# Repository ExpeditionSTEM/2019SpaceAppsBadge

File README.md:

# 2019SpaceAppsBadge
PLEASE STAY TUNED FOR UPDATES!  I WILL GET THIS REPO UPDATED BY 10/29.

A description of the 2019 Space Apps Trophy made for the Huntsville Main Stage

LIST OF COMPONENTS:

CUSTOM:

Custom Printed Circuit Board (PCB) - Designed by Andrew Denio. Produced by JLCPCB.com See "EAGLE" folder for files.

ATTINY 85-20PU Microcontroller 8 pin DIP: https://www.amazon.com/gp/product/B06W9JBJJ6

SSD1306 128x32 pixel i2c OLED Display https://www.amazon.com/gp/product/B07WHVYWXS/

3xAAA Enclosed Battery Case https://www.amazon.com/gp/product/B07M8RV9DC

MISC:

Photoresistor (Light Sensor) 5 mm GM5539 5539 https://www.amazon.com/dp/B01N7V536K

Slide Switch 3 Pin 2 Position SPDT with PCB Panel for Arduino 0.5 Amp, 50V DC, 2 mm https://www.amazon.com/gp/product/B079D58DB3/

FROM JLCPCB (mounted through SMT assembly):

WS2812B-V3 - 5050 LIGHT EMITTING DIODE (LED) RED/GREEN/BLUE SMD

8 pin Female Header to re-flash ATTINY chip

FOR 'THROUGH-HOLE' BOARD:

470 OHM 1/4 Watt resistor

10 KOHM 1/4 Watt resistor

6mm x 6mm Tactile Buttons

10uF 25V Capacitor

FOR 'SMD' BOARD:

TACTILE SWITCHES SPST 5.10MM X 5.10MM 0.40MM 50MA @ 12VDC SMD

Multilayer Ceramic Capacitor - SMD/SMT 10UF 25V 0805 ROHS

CHIP RESISTOR - SURFACE MOUNT 10KOHMS ±1% 1/8W 0805 ROHS

CHIP RESISTOR - SURFACE MOUNT 470OHMS ±1% 1/8W 0805 ROHS

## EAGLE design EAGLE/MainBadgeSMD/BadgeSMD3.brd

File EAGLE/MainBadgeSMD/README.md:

This is the badge that was 'fully' assembled.  Most of the badge was assembled by JLCPCB, but some components were hand soldered/mounted.

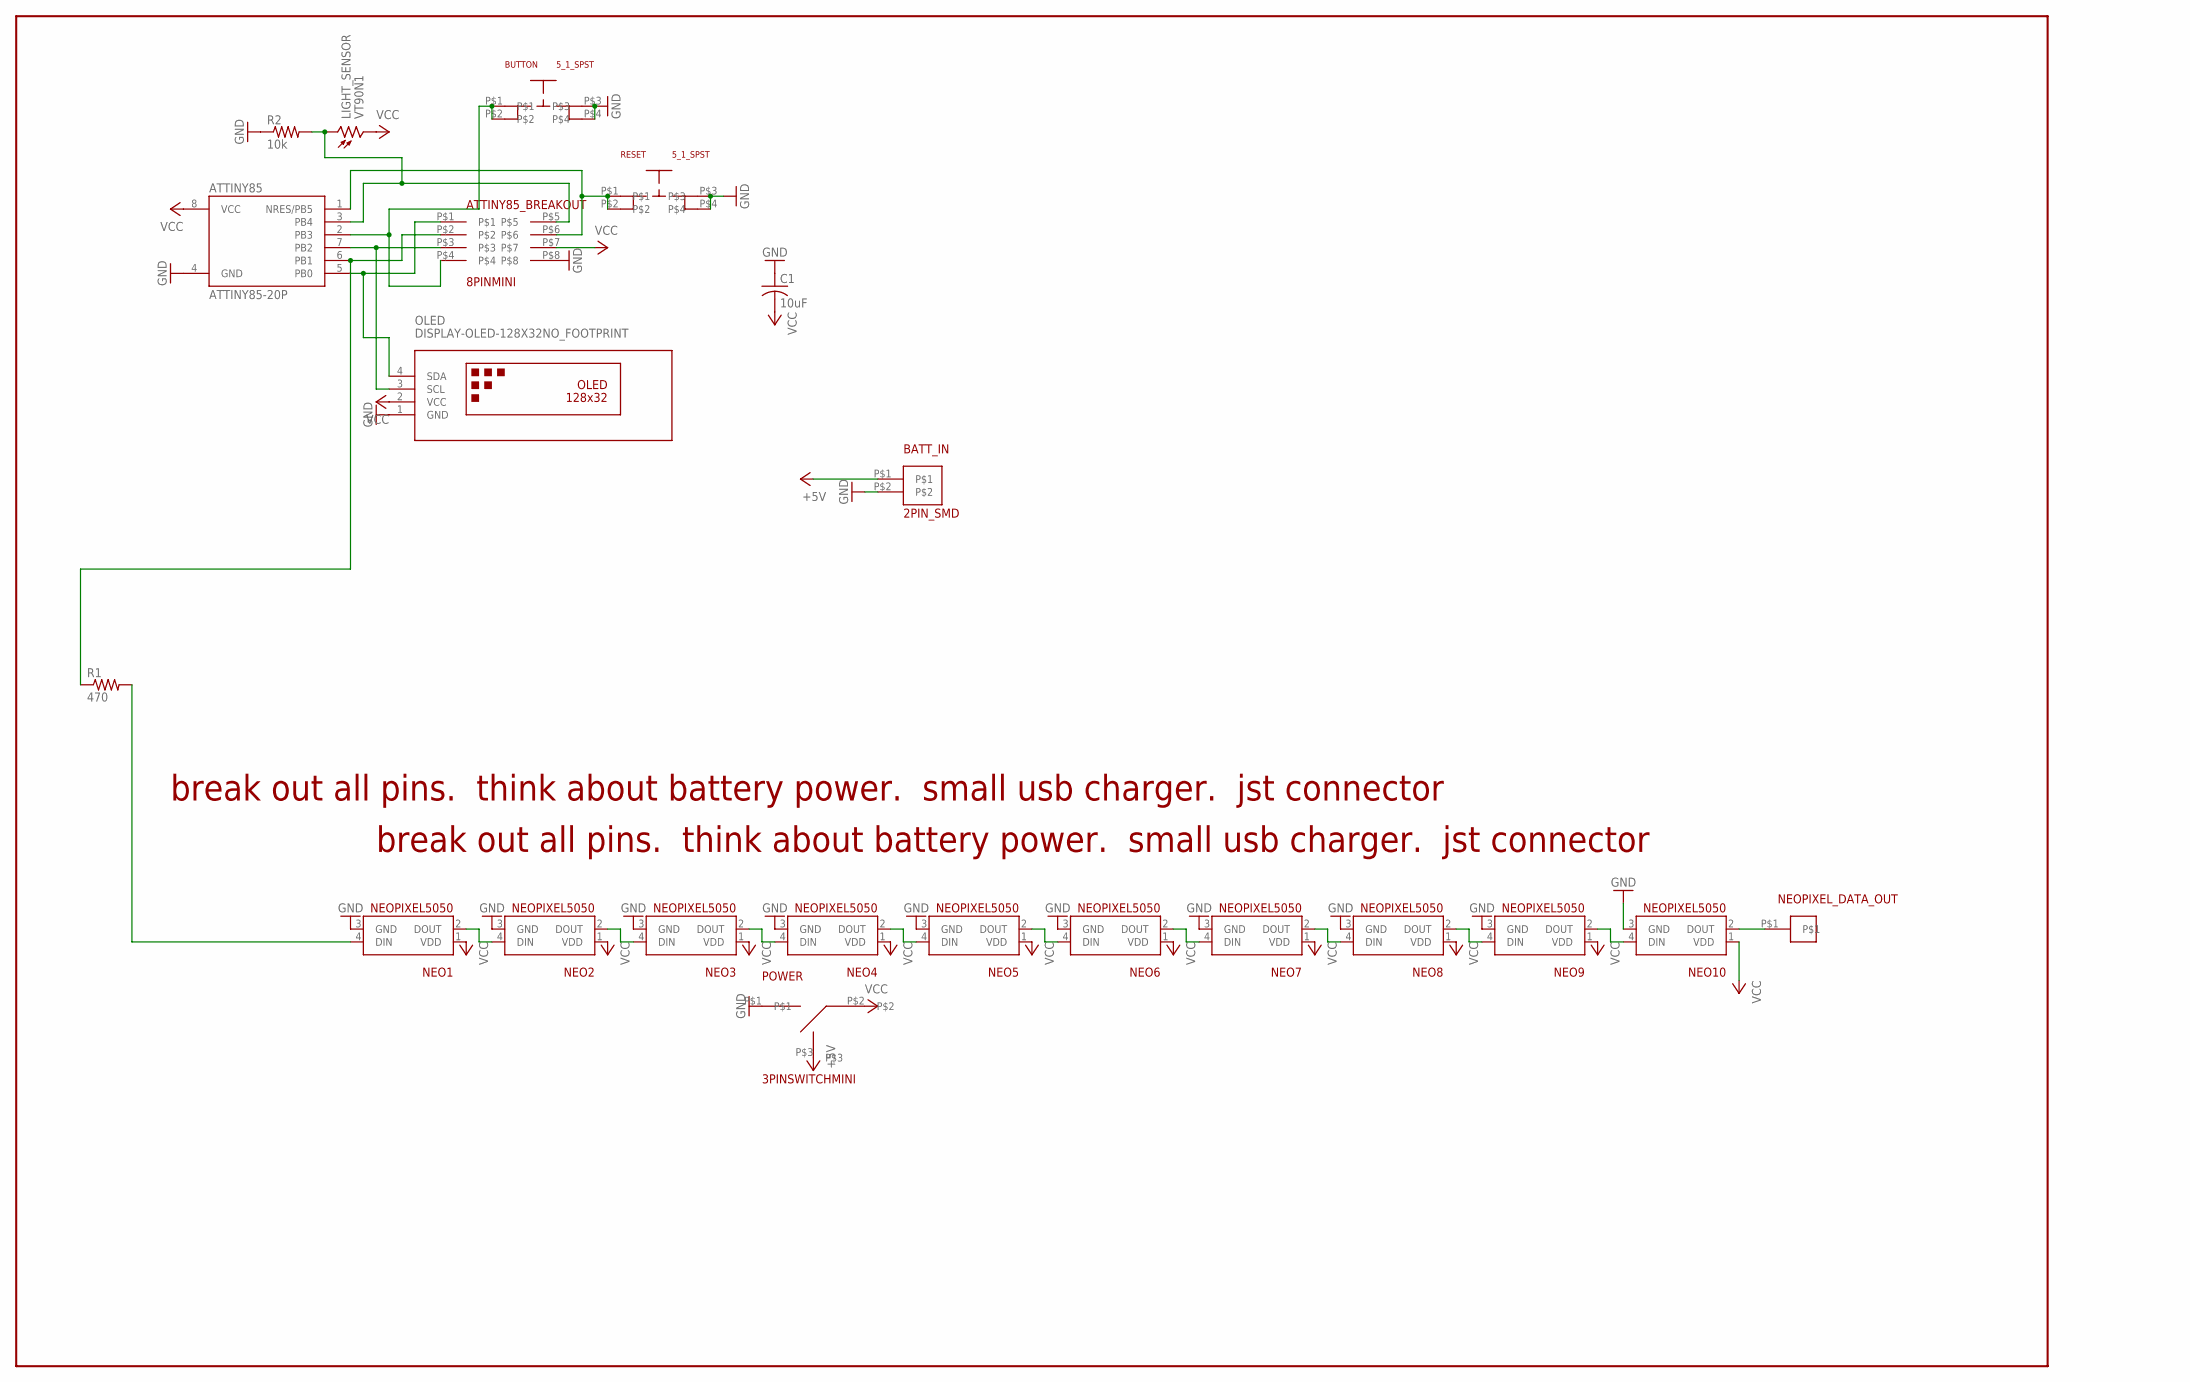
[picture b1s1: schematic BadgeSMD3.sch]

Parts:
ATTINY85: ATTINY85-20P; PDIP08_300MIL
ATTINY85_BREAKOUT: 8PINMINI
BATT_IN: 2PIN_SMD
BUTTON: 5_1_SPST
C1: 10uF; C0805
LIGHT_SENSOR: VT90N1; VT900
NEO1, NEO2, NEO3, NEO4, NEO5, NEO6, NEO7, NEO8, NEO9, NEO10: NEOPIXEL5050
NEOPIXEL_DATA_OUT: 1PINMINI
OLED: DISPLAY-OLED-128X32NO_FOOTPRINT; DISPLAY-OLED-128X32_NO_FOOTPRINT
POWER: 3PINSWITCHMINI; 3PINMINI
R1: 470; M0805
R2: 10k; M0805
RESET: 5_1_SPST

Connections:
+5V: BATT_IN.P$1, POWER.P$3
GND: ATTINY85.4 (GND), ATTINY85_BREAKOUT.P$8, BATT_IN.P$2, BUTTON.P$3, BUTTON.P$4, C1.1, NEO1.3 (GND), NEO2.3 (GND), NEO3.3 (GND), NEO4.3 (GND), NEO5.3 (GND), NEO6.3 (GND), NEO7.3 (GND), NEO8.3 (GND), NEO9.3 (GND), NEO10.3 (GND), OLED.1 (GND), POWER.P$1, R2.1, RESET.P$3, RESET.P$4
unnamed: ATTINY85.5 (PB0), ATTINY85_BREAKOUT.P$1, OLED.4 (SDA)
unnamed: NEO1.4 (DIN), R1.2
unnamed: ATTINY85.7 (PB2), ATTINY85_BREAKOUT.P$3, OLED.3 (SCL)
unnamed: ATTINY85.2 (PB3), ATTINY85_BREAKOUT.P$4, BUTTON.P$1, BUTTON.P$2
unnamed: ATTINY85.3 (PB4), ATTINY85_BREAKOUT.P$5, LIGHT_SENSOR.1, R2.2
unnamed: ATTINY85.1 (NRES/PB5), ATTINY85_BREAKOUT.P$6, RESET.P$1, RESET.P$2
unnamed: NEO1.2 (DOUT), NEO2.4 (DIN)
unnamed: ATTINY85.6 (PB1), ATTINY85_BREAKOUT.P$2, R1.1
unnamed: NEO2.2 (DOUT), NEO3.4 (DIN)
unnamed: NEO3.2 (DOUT), NEO4.4 (DIN)
unnamed: NEO4.2 (DOUT), NEO5.4 (DIN)
unnamed: NEO5.2 (DOUT), NEO6.4 (DIN)
unnamed: NEO6.2 (DOUT), NEO7.4 (DIN)
unnamed: NEO7.2 (DOUT), NEO8.4 (DIN)
unnamed: NEO8.2 (DOUT), NEO9.4 (DIN)
unnamed: NEO9.2 (DOUT), NEO10.4 (DIN)
unnamed: NEO10.2 (DOUT), NEOPIXEL_DATA_OUT.P$1
VCC: ATTINY85.8 (VCC), ATTINY85_BREAKOUT.P$7, C1.2, LIGHT_SENSOR.2, NEO1.1 (VDD), NEO2.1 (VDD), NEO3.1 (VDD), NEO4.1 (VDD), NEO5.1 (VDD), NEO6.1 (VDD), NEO7.1 (VDD), NEO8.1 (VDD), NEO9.1 (VDD), NEO10.1 (VDD), OLED.2 (VCC), POWER.P$2

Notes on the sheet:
break out all pins. think about battery power. small usb charger. jst connector

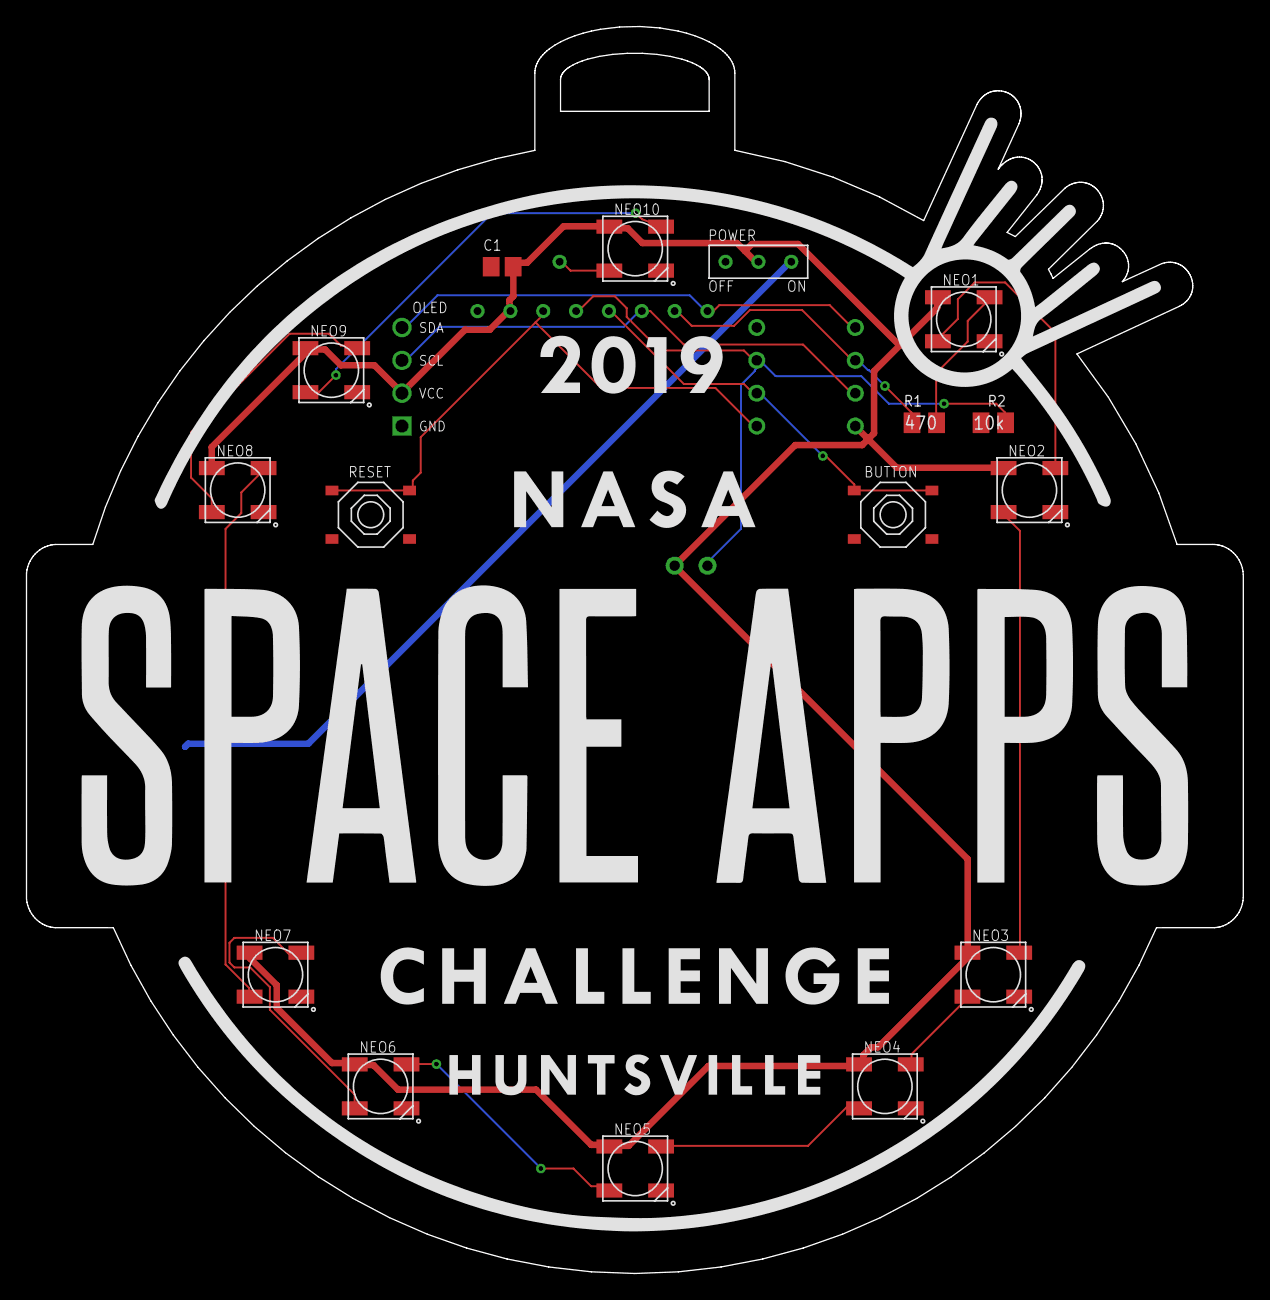
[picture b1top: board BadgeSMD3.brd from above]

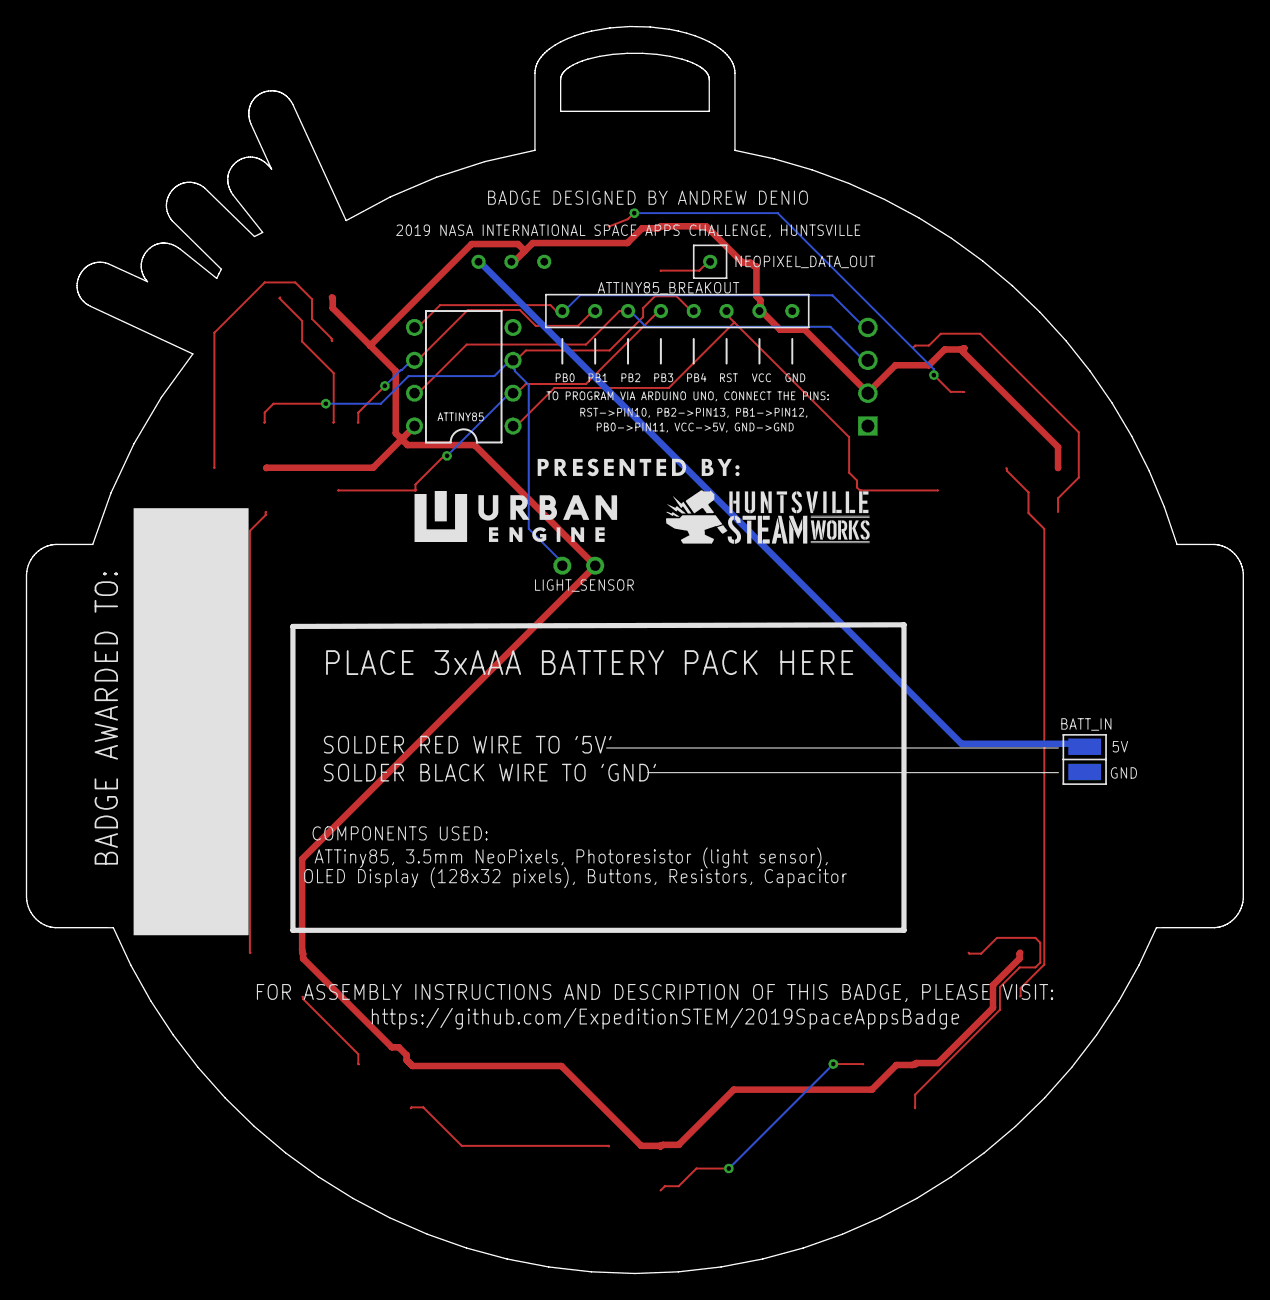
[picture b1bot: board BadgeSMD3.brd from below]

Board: 2 copper layers, 94.1 x 96.4 mm, 22 parts (5 on the bottom side), 20 nets.

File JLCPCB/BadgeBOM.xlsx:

Comment | Designator | Footprint | LCSC Part #（optional）
10uF | C1 | 0805 | C15850
10KO | R2 | 0805 | C17414
470O | R1 | 0805 | C17710
NEOPIXEL5050 | NEO1 | LED-4_5050 | C114585
NEOPIXEL5050 | NEO2 | LED-4_5050 | C114585
NEOPIXEL5050 | NEO3 | LED-4_5050 | C114585
NEOPIXEL5050 | NEO4 | LED-4_5050 | C114585
NEOPIXEL5050 | NEO5 | LED-4_5050 | C114585
NEOPIXEL5050 | NEO6 | LED-4_5050 | C114585
NEOPIXEL5050 | NEO7 | LED-4_5050 | C114585
NEOPIXEL5050 | NEO8 | LED-4_5050 | C114585
NEOPIXEL5050 | NEO9 | LED-4_5050 | C114585
NEOPIXEL5050 | NEO10 | LED-4_5050 | C114585
BUTTON_B | BUTTON | SMD-SW-4_5.1x5.1x2.0 | C318884
BUTTON_A | RESET | SMD-SW-4_5.1x5.1x2.0 | C318884

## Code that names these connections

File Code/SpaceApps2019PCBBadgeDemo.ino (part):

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  GND - BATTERY NEGATIVE TERMINAL
  VCC - BATTERY POSITIVE TERMINAL
  PBO - I2C BUS - SDA
  PB1 - NEOPIXEL OUT
  PB2 - I2C BUS - SCL
  PB3 - BUTTON INPUT
  PB4 - LIGHT SENSOR INPUT
  PB5 - RESET BUTTON
  
 */

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
                          

#define LIGHT_SENSOR_PIN A2  // THIS IS PB4, BUT MUST LABEL IT A2 IN ORDER FOR THE ANALOG FUNCTIONS TO WORK
int lightSensorValue = 0;


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

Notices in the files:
Code/SpaceApps2019PCBBadgeDemo.ino:
MIT license, all text above must be included in any redistribution
